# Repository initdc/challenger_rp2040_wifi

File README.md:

# The ESP210 ESP8266 modile

## ESP210 information
The ESP210 is a micro controller board packed with loads of functionality in a very small format for your projects that requires a WiFi connection.

The main controller of this board is the ESP8266 from Espressif connected to 4MByte of FLASH memory and with a total of 80KByte of internal SRAM. The ESP8266 MCU is built around the Tensilica Diamond Standard 106Micro's running at up to 160 MHz. It has a few basic digital peripherals and interfaces such as high speed SPI, I2C and a timer.

## ESP210 Key features
- Tensilica Diamond Standard 106Micro running at up to 160MHz
- 4 MB Flash, 80 KB RAM
- 2.4GHz WiFi modem
- UART, SPI, I2C
- PWM
- 10 - bit ADC
- USB 2.0

## The board

### WiFi solution
The WiFi radio is integrated onto the ESP8266 and you can read more about this at Espressifs website.

### Power
There is an onboard LDO that runs the onboard electronic devices.

### Other stuff
The ESP8266 does not have USB natively so on board there is a USB to serial bridge chip from Silabs called CP2104. This chip handles all the communication towards the PC. It also makes sure the ESP8266 is reset and that the boot mode pin is set correctly when you need to upload new firmware to the board.

### Pinout

### Software support
The board is supported by both the Arduino environment as well as PlatforIO.

## License
This design covered by the CERN Open Hardware Licence v1.2 and a copy of this license is also available in this repo.

## iLabs

### About us
Invector Labs is a small Swedish engineering company that designs and build electronic devices for hobbyists as well as small and medium sized businesses.

For more information about this board you can visit the product page at our [website](https://ilabs.se/product/esp8266-module/)

Questions about this product can be addressed to <oshwa@ilabs.se>.

/* EOF */

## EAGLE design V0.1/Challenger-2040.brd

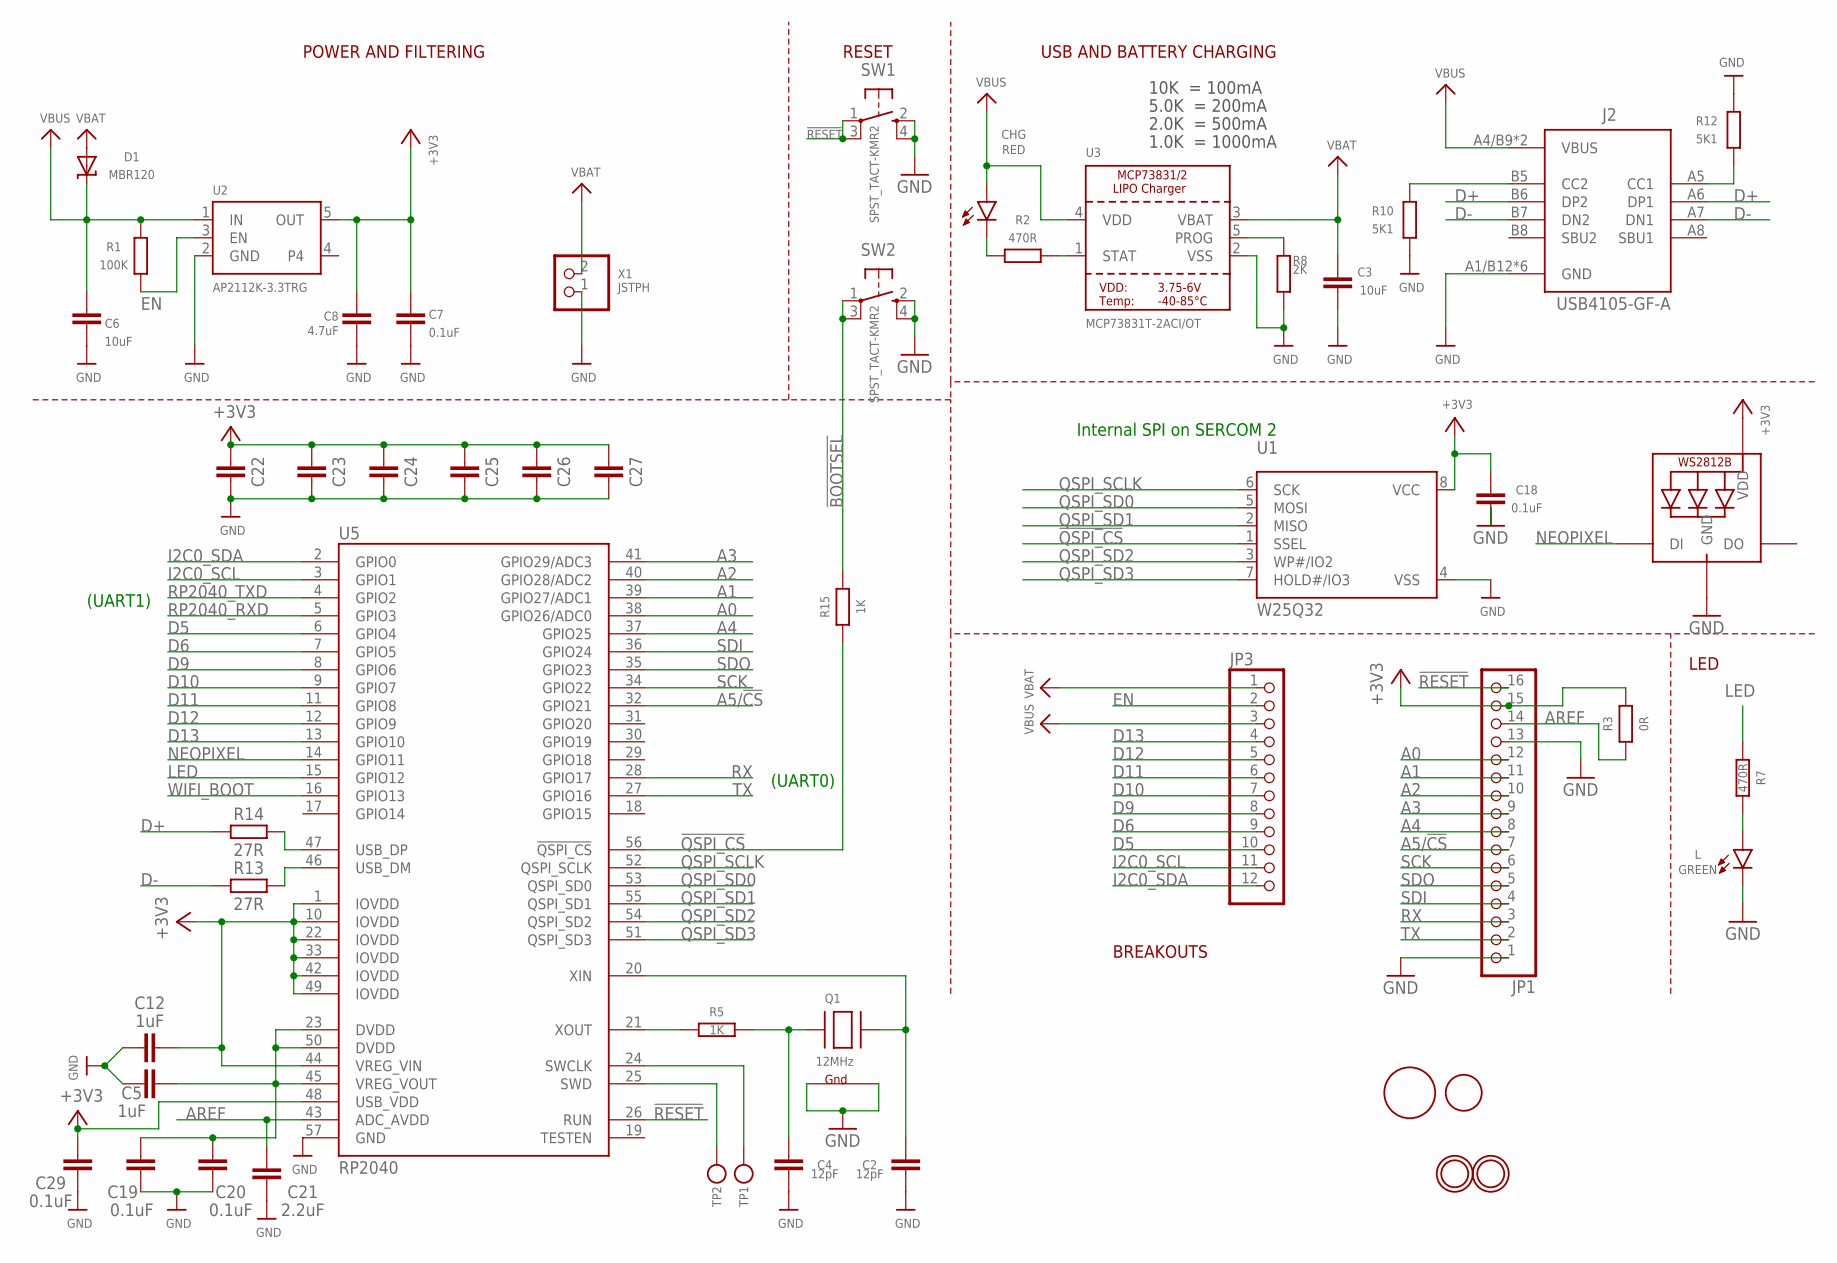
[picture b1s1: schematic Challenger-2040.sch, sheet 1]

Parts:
C2, C4: 12pF; CAPC1005X60
C3, C6: 10uF; CAPC1608X85
C5, C12: 1uF; CAPC1005X60
C7, C18, C19, C20, C29: 0.1uF; CAPC1005X60
C8: 4.7uF; CAPC1005X60
C21: 2.2uF; CAPC1005X60
C22, C23, C24, C25, C26, C27: C_CHIP-0402(1005-METRIC); CAPC1005X60
CHG: RED; CHIPLED_0603
D1: MBR120; SOD-123
J2: USB4105-GF-A; GCT_USB4105-GF-A
JP1: HEADER-1X16ROUND; 1X16_ROUND
JP3: HEADER-1X12; 1X12_ROUND
L: GREEN; CHIPLED_0603
LED1: WS2812B3535; LED3535
LOGO1: CHALENGER-11MM; CHALLENGER
Q1: 12MHz; NX3225
R1: 100K; RESC1005X40
R2, R7: 470R; RESC1005X40
R3: 0R; RESC1005X40
R5, R15: 1K; RESC1005X40
R8: 2K; RESC1005X40
R10, R12: 5K1; RESC1005X40
R13, R14: 27R; RESC1005X40
SW1, SW2: SPST_TACT-KMR2; KMR2
TP1, TP2: TESTPOINTROUND1.5MM; TESTPOINT_ROUND_1.5MM
U1: W25Q32; SOIC8_208MIL
U2: AP2112K-3.3TRG; SOT23-5
U3: MCP73831T-2ACI/OT; SOT23-5
U5: RP2040; QFN40P700X700X90-57T310N
U$11: CHAL-TEXT
U$31, U$32: MOUNTINGHOLE2.5; MOUNTINGHOLE_2.5_PLATED
X1: JSTPH; JSTPH2

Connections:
!BOOTSEL: R15.2, SW2.1, SW2.3 (P1)
!QSPI_CS: R15.1, U1.1 (SSEL), U5.56 (!QSPI_CS)
!RESET: JP1.16, SW1.1, SW1.3 (P1), U5.26 (RUN)
+3V3: C7.1, C8.1, C12.2, C18.1, C22.2, C23.2, C24.2, C25.2, C26.2, C27.2, C29.2, JP1.15, LED1.2 (VDD), R3.2, U1.8 (VCC), U2.5 (OUT), U5.1 (IOVDD), U5.10 (IOVDD), U5.22 (IOVDD), U5.33 (IOVDD), U5.42 (IOVDD), U5.44 (VREG_VIN), U5.48 (USB_VDD), U5.49 (IOVDD); also elsewhere on the board
A0: JP1.12, U5.38 (GPIO26/ADC0)
A1: JP1.11, U5.39 (GPIO27/ADC1)
A2: JP1.10, U5.40 (GPIO28/ADC2)
A3: JP1.9, U5.41 (GPIO29/ADC3)
A4: JP1.8, U5.37 (GPIO25)
A5/!CS: JP1.7, U5.32 (GPIO21)
AREF: C21.2, JP1.14, R3.1, U5.43 (ADC_AVDD)
D5: JP3.10, U5.6 (GPIO4)
D6: JP3.9, U5.7 (GPIO5)
D9: JP3.8, U5.8 (GPIO6)
D10: JP3.7, U5.9 (GPIO7)
D11: JP3.6, U5.11 (GPIO8)
D12: JP3.5, U5.12 (GPIO9)
D13: JP3.4, U5.13 (GPIO10)
D+: J2.A6 (DP1), J2.B6 (DP2), R14.1
D-: J2.A7 (DN1), J2.B7 (DN2), R13.1
EN: JP3.2, R1.2, U2.3 (EN)
GND: C2.2, C3.2, C4.2, C5.1, C6.2, C7.2, C8.2, C12.1, C18.2, C19.1, C20.1, C21.1, C22.1, C23.1, C24.1, C25.1, C26.1, C27.1, C29.1, J2.A1/B12 (GND), J2.B1/A12 (GND), J2.G1 (GND), J2.G2 (GND), J2.G3 (GND), J2.G4 (GND), JP1.1, JP1.13, L.C, LED1.4 (GND), Q1.2 (G2), Q1.4 (G1), R8.2, R10.2, R12.1, SW1.2 (S), SW1.4 (S1), SW2.2 (S), SW2.4 (S1), U1.4 (VSS), U2.2 (GND), U3.2 (VSS), U5.57 (GND), X1.1; also elsewhere on the board
I2C0_SCL: JP3.11, U5.3 (GPIO1)
I2C0_SDA: JP3.12, U5.2 (GPIO0)
LED: R7.1, U5.15 (GPIO12)
unnamed: CHG.C, R2.1
unnamed: L.A, R7.2
unnamed: R2.2, U3.1 (STAT)
unnamed: R8.1, U3.5 (PROG)
unnamed: R13.2, U5.46 (USB_DM)
unnamed: R14.2, U5.47 (USB_DP)
unnamed: J2.B5 (CC2), R10.1
unnamed: J2.A5 (CC1), R12.2
unnamed: C2.1, Q1.3 (X2), U5.20 (XIN)
unnamed: TP1.P$1, U5.24 (SWCLK)
unnamed: TP2.P$1, U5.25 (SWD)
unnamed: C4.1, Q1.1 (X1), R5.2
unnamed: R5.1, U5.21 (XOUT)
unnamed: C5.2, C19.2, C20.2, U5.23 (DVDD), U5.45 (VREG_VOUT), U5.50 (DVDD)
NEOPIXEL: LED1.1 (DI), U5.14 (GPIO11)
QSPI_SCLK: U1.6 (SCK), U5.52 (QSPI_SCLK)
QSPI_SD0: U1.5 (MOSI), U5.53 (QSPI_SD0)
QSPI_SD1: U1.2 (MISO), U5.55 (QSPI_SD1)
QSPI_SD2: U1.3 (WP#/IO2), U5.54 (QSPI_SD2)
QSPI_SD3: U1.7 (HOLD#/IO3), U5.51 (QSPI_SD3)
RP2040_RXD: U5.5 (GPIO3); also elsewhere on the board
RP2040_TXD: U5.4 (GPIO2); also elsewhere on the board
RX: JP1.3, U5.28 (GPIO17)
SCK: JP1.6, U5.34 (GPIO22)
SDI: JP1.4, U5.36 (GPIO24)
SDO: JP1.5, U5.35 (GPIO23)
TX: JP1.2, U5.27 (GPIO16)
VBAT: C3.1, D1.A, JP3.1, U3.3 (VBAT), X1.2
VBUS: C6.1, CHG.A, D1.C, J2.A4/B9 (VBUS), J2.B4/A9 (VBUS), JP3.3, R1.1, U2.1 (IN), U3.4 (VDD)
WIFI_BOOT: U5.16 (GPIO13); also elsewhere on the board

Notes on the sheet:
POWER AND FILTERING
RESET
10K = 100mA
5.0K = 200mA
2.0K = 500mA
1.0K = 1000mA
USB AND BATTERY CHARGING
BREAKOUTS
LED
Internal SPI on SERCOM 2
(UART0)
(UART1)

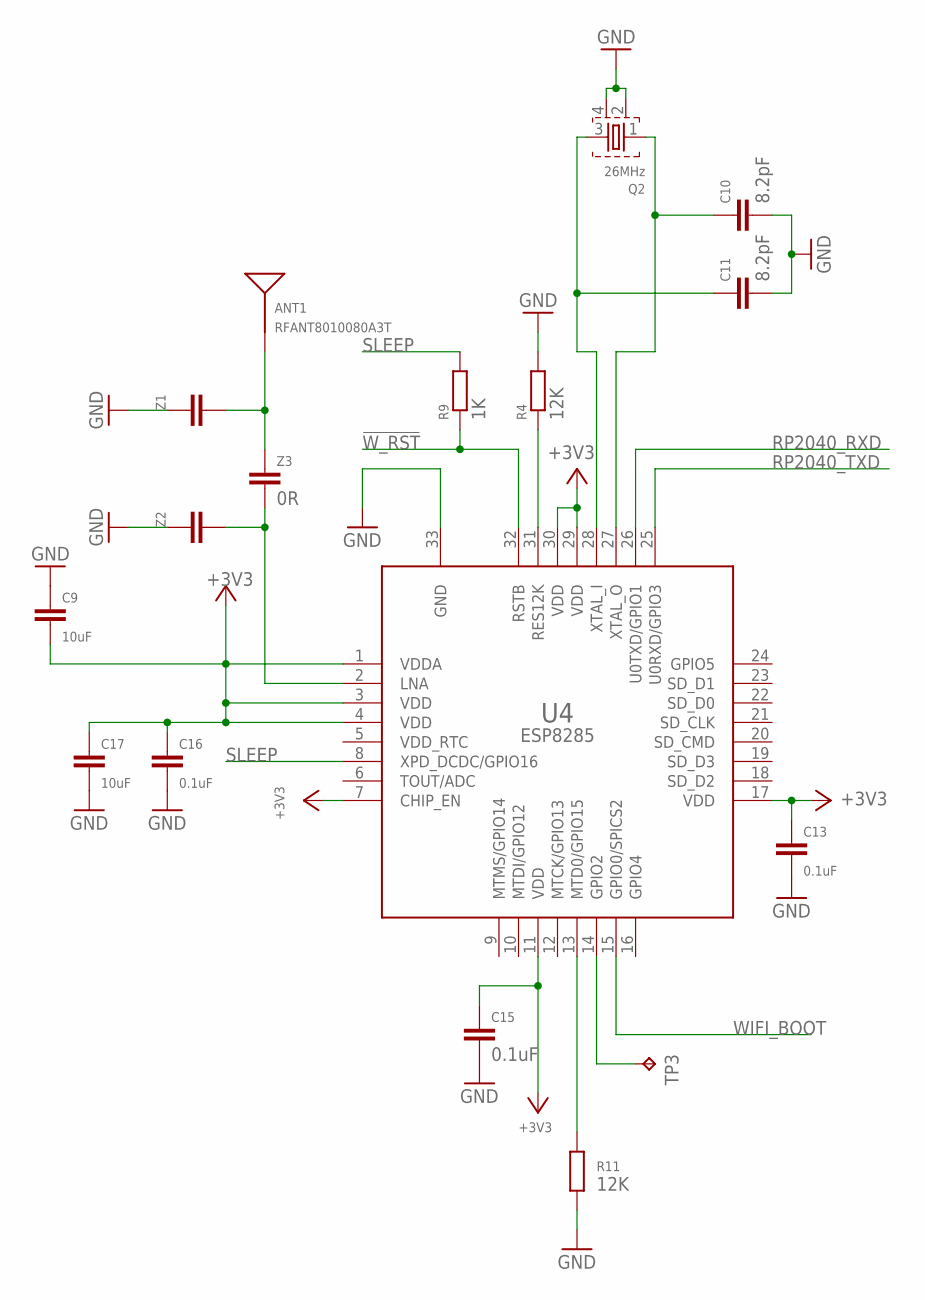
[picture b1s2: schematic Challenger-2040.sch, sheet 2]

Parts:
ANT1: RFANT8010080A3T; ANTENNA-CHIP6
C9, C17: 10uF; CAPC1608X85
C10, C11: 8.2pF; CAPC1005X60
C13, C15, C16: 0.1uF; CAPC1005X60
Q2: 26MHz; FA-128
R4, R11: 12K; RESC1005X40
R9: 1K; RESC1005X40
TP3: TPB1,27; B1,27
U4: ESP8285; SLP32
Z1, Z2: C_CHIP-0402(1005-METRIC); CAPC1005X60
Z3: 0R; CAPC1005X60

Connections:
!W_RST: R9.1, U4.32 (RSTB)
+3V3: C9.2, C13.1, C15.1, C16.1, C17.1, U4.1 (VDDA), U4.3 (VDD), U4.4 (VDD), U4.7 (CHIP_EN), U4.11 (VDD), U4.17 (VDD), U4.29 (VDD), U4.30 (VDD); also elsewhere on the board
GND: C9.1, C10.2, C11.2, C13.2, C15.2, C16.2, C17.2, Q2.2, Q2.4, R4.2, R11.2, U4.33 (GND), Z1.1, Z2.1; also elsewhere on the board
unnamed: R4.1, U4.31 (RES12K)
unnamed: C10.1, Q2.1, U4.27 (XTAL_O)
unnamed: TP3.TP, U4.14 (GPIO2)
unnamed: C11.1, Q2.3, U4.28 (XTAL_I)
unnamed: R11.1, U4.13 (MTD0/GPIO15)
RF1: U4.2 (LNA), Z2.2, Z3.2
RF2: ANT1.1, Z1.2, Z3.1
RP2040_RXD: U4.26 (U0TXD/GPIO1); also elsewhere on the board
RP2040_TXD: U4.25 (U0RXD/GPIO3); also elsewhere on the board
SLEEP: R9.2, U4.8 (XPD_DCDC/GPIO16)
WIFI_BOOT: U4.15 (GPIO0/SPICS2); also elsewhere on the board

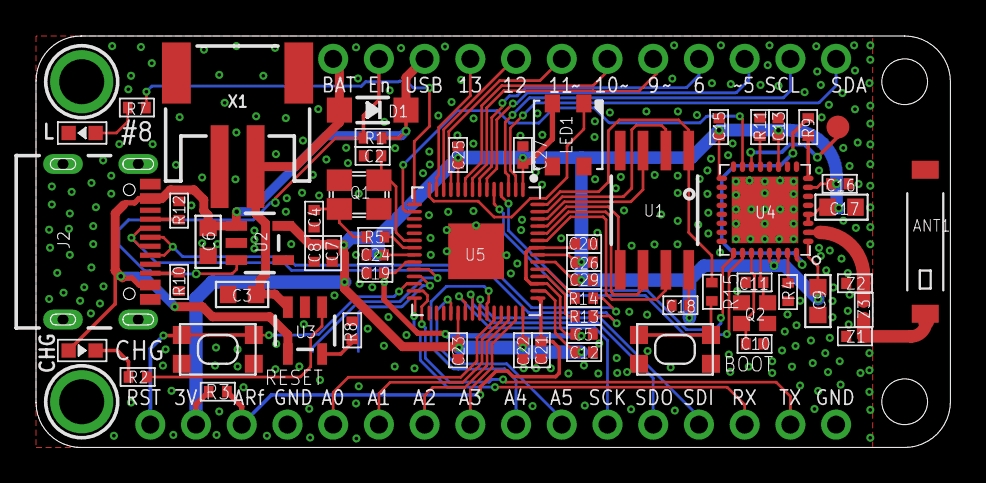
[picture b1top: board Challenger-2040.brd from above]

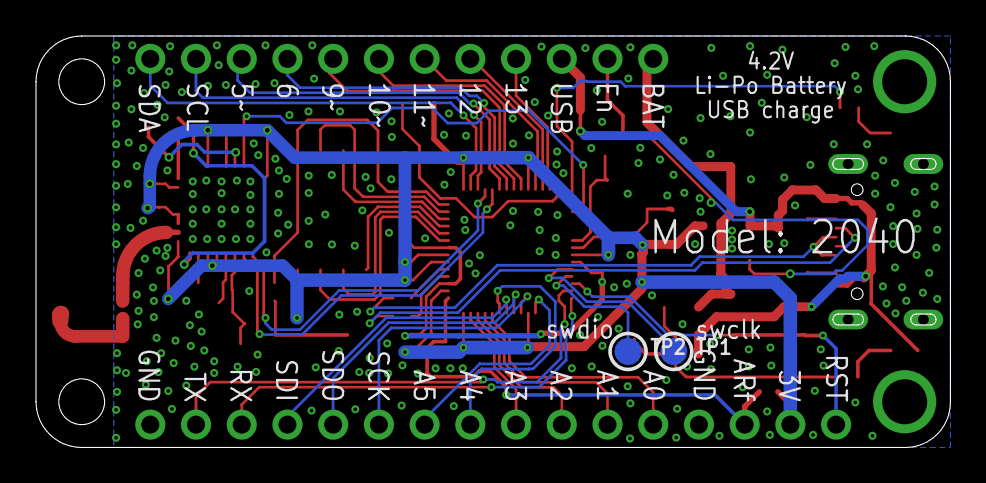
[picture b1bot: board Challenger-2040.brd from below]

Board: 2 copper layers, 50.8 x 22.9 mm, 68 parts (4 on the bottom side), 64 nets.

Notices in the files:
parts and their libraries:
microbuilder: This work is placed in the public domain, and may be freely used for commercial and non-commercial work with the following conditions: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
SparkFun-RF: Licensing: CC v3.0 Share-Alike You are welcome to use this library for commercial purposes.
